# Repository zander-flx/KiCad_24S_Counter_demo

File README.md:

# 24-Second Countdown Timer (TTL Logic)  
## Overview  
This project is a 24-second countdown timer implemented using classic TTL logic ICs. The design is captured and laid out in KiCad and drives common-cathode 7-segment displays through BCD decoding logic. The system includes user control via a slide switch (enable) and a tactile push button (load data).  
The project demonstrates the practical use of up/down counters, BCD-to-7-segment decoding, and basic control logic.  

## Functional Description  
### Counter Operation  
The 74192 counter is configured to perform a count-down operation.  
The timer starts from a preset value corresponding to 24 seconds.  
Each clock pulse decrements the count by one.  
### Display Logic  
The 4-bit BCD output from the 74192 feeds directly into the 7448.  
The 7448 decodes the BCD value and drives the common-cathode 7-segment display.  
Segment current limiting is handled by external resistors.  

## Controls  
### Slide Switch (Enable)  
ON: Enables the countdown operation  
OFF: Pauses or disables the counter  
### Tact Switch (load data)  
Used to manually load the data corresponding to 24 decimal digit.

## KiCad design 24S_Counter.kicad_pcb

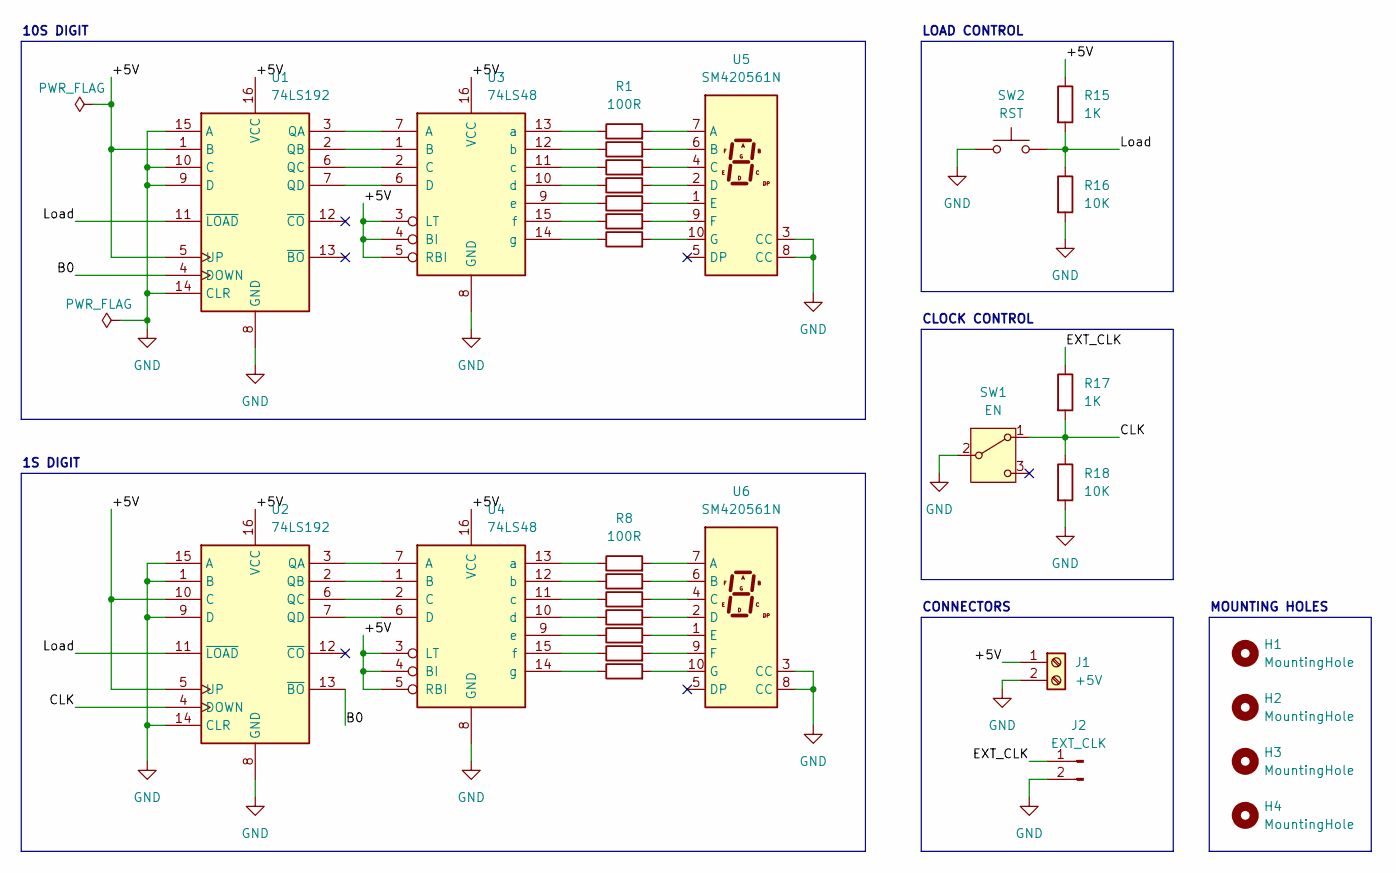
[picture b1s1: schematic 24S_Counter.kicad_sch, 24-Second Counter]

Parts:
H1, H2, H3, H4: MountingHole; MountingHole_2.2mm_M2
J1: +5V; Terminal_Block_5mm
J2: EXT_CLK; PinHeader_1x02_P2.54mm_Vertical
R1, R2, R3, R4, R5, R6, R7, R8, R9, R10, R11, R12, R13, R14: 100R; R_1206_3216Metric_Pad1.30x1.75mm_HandSolder
R15, R17: 1K; R_1206_3216Metric_Pad1.30x1.75mm_HandSolder
R16, R18: 10K; R_1206_3216Metric_Pad1.30x1.75mm_HandSolder
SW1: EN; slide_switch_2.54mm
SW2: RST; tact_switch_5mm
U1, U2: 74LS192
U3, U4: 74LS48
U5, U6: SM420561N; 7SegmentLED_LTS6760_LTS6780

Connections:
/+5V: J1.1, R15.1, U1.1 (B), U1.5 (UP), U1.16 (VCC), U2.5 (UP), U2.10 (C), U2.16 (VCC), U3.3 (LT), U3.4 (BI), U3.5 (RBI), U3.16 (VCC), U4.3 (LT), U4.4 (BI), U4.5 (RBI), U4.16 (VCC)
/B0: U1.4 (DOWN), U2.13 (~BO)
/CLK: R17.2, R18.1, SW1.1 (A), U2.4 (DOWN)
/EXT_CLK: J2.1, R17.1
/Load: R15.2, R16.1, SW2.2, U1.11 (~LOAD), U2.11 (~LOAD)
GND: J1.2, J2.2, R16.2, R18.2, SW1.2 (B), SW2.1, U1.8 (GND), U1.9 (D), U1.10 (C), U1.14 (CLR), U1.15 (A), U2.1 (B), U2.8 (GND), U2.9 (D), U2.14 (CLR), U2.15 (A), U3.8 (GND), U4.8 (GND), U5.3 (CC), U5.8 (CC), U6.3 (CC), U6.8 (CC)
unnamed: U1.3 (QA), U3.7 (A)
unnamed: U1.2 (QB), U3.1 (B)
unnamed: U1.6 (QC), U3.2 (C)
unnamed: U1.7 (QD), U3.6 (D)
unnamed: U2.3 (QA), U4.7 (A)
unnamed: U2.2 (QB), U4.1 (B)
unnamed: U2.6 (QC), U4.2 (C)
unnamed: U2.7 (QD), U4.6 (D)
unnamed: R1.1, U3.13 (a)
unnamed: R2.1, U3.12 (b)
unnamed: R3.1, U3.11 (c)
unnamed: R4.1, U3.10 (d)
unnamed: R5.1, U3.9 (e)
unnamed: R6.1, U3.15 (f)
unnamed: R7.1, U3.14 (g)
unnamed: R8.1, U4.13 (a)
unnamed: R9.1, U4.12 (b)
unnamed: R10.1, U4.11 (c)
unnamed: R11.1, U4.10 (d)
unnamed: R12.1, U4.9 (e)
unnamed: R13.1, U4.15 (f)
unnamed: R14.1, U4.14 (g)
unnamed: R1.2, U5.7 (A)
unnamed: R2.2, U5.6 (B)
unnamed: R3.2, U5.4 (C)
unnamed: R4.2, U5.2 (D)
unnamed: R5.2, U5.1 (E)
unnamed: R6.2, U5.9 (F)
unnamed: R7.2, U5.10 (G)
unnamed: R8.2, U6.7 (A)
unnamed: R9.2, U6.6 (B)
unnamed: R10.2, U6.4 (C)
unnamed: R11.2, U6.2 (D)
unnamed: R12.2, U6.1 (E)
unnamed: R13.2, U6.9 (F)
unnamed: R14.2, U6.10 (G)

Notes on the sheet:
MOUNTING HOLES
LOAD CONTROL
CONNECTORS
CLOCK CONTROL
1S DIGIT
10S DIGIT

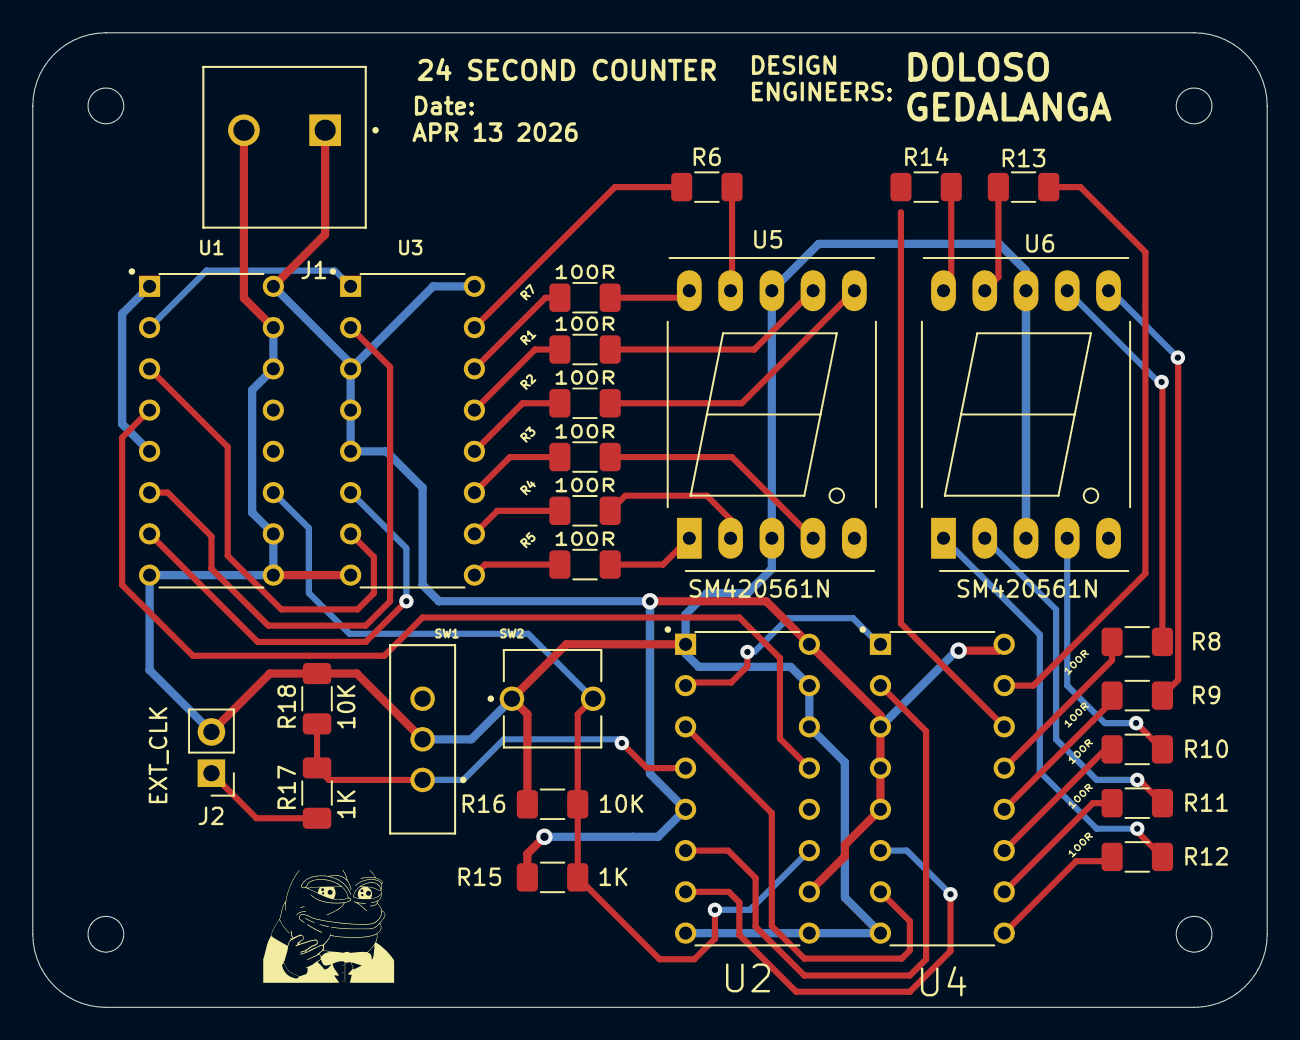
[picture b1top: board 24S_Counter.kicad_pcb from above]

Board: 2 copper layers, 76.0 x 60.0 mm, 32 parts (0 on the bottom side), 42 nets.

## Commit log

2026-04-13 Updated 04/13/26 (17:06)
